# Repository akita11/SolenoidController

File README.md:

# SolenoidController

・ソレノイドやDCモータを4個、制御できるボード。単体でスイッチでON/OFFできる。
・各種マイコン(Arduino, micro:bit, RaspberryPi, IchigoJam, Grove)からも制御できる。
・電源は24Vまで（使用するソレノイドにあわせる）
- オプションで、USB Type-C PDからの給電もできる（検証は不十分）

# Author

Junichi Akita (@akita11, akita@ifdl.jp)

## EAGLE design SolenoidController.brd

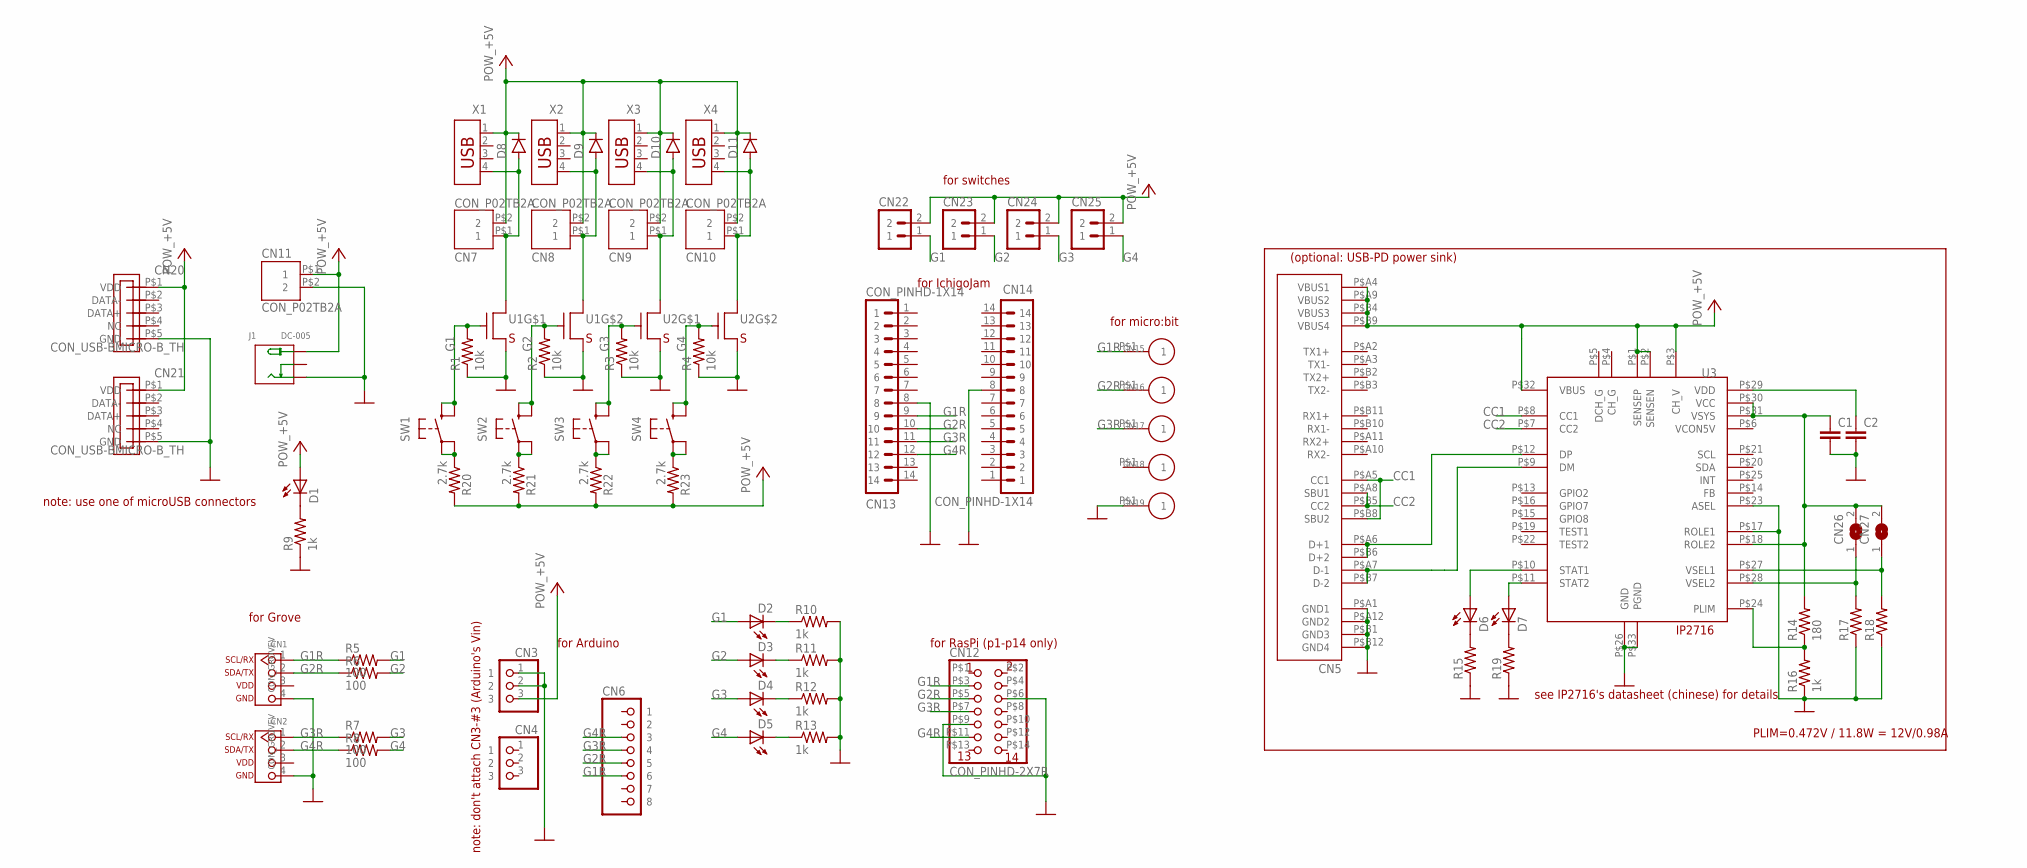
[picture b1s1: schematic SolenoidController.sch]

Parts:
C1, C2: CAP0603; 0603
CN1, CN2: CON_GROVEV; CON_GROVE_V
CN3, CN4: CON_PINHD-1X3R; 1X03R
CN5: CON_USB-C; USB-C_24P
CN6: CON_PINHD-1X8R; 1X08R
CN7, CN8, CN9, CN10, CN11: CON_P02TB2A; TERM_BLOCK_2P
CN12: CON_PINHD-2X7R; 2X7R
CN13, CN14: CON_PINHD-1X14; 1X14
CN15, CN16, CN17, CN18, CN19: CON_P01TH04MM; TH4MM
CN20, CN21: CON_USB-BMICRO-B_TH; USB-MICROB-TH
CN22, CN23, CN24, CN25: CON_PINHD-1X2PTH; SPARKFUN_1X02
CN26, CN27: JUMPER_SJ
D1, D2, D3, D4, D5: LED5MM; SPARKFUN_LED5MM
D6, D7: LED0603; SPARKFUN_LED-0603
D8, D9, D10, D11: DIODESOD123FL; SOD123FL
J1: DC-005; DCJ3P-14.2X11.0X9.0MM
R1, R2, R3, R4: 10k; 0603
R5, R6, R7, R8: 100; 0603
R9, R10, R11, R12, R13, R16: 1k; 0603
R14: 180; 0603
R15, R17, R18, R19: RES0603; 0603
R20, R21, R22, R23: 2.7k; 0603
SW1, SW2, SW3, SW4: SW_TACTSMD_B3FS4; SW_B3FS-4
U1, U2: TR_NMOS_IRF7103; SO08
U3: PMU_IP2716; QFN32E
X1, X2, X3, X4: CON_USB-A; USB-A

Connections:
+5V: CN3.3, CN5.P$A4 (VBUS1), CN5.P$A9 (VBUS2), CN5.P$B4 (VBUS3), CN5.P$B9 (VBUS4), CN7.P$2 (2), CN8.P$2 (2), CN9.P$2 (2), CN10.P$2 (2), CN11.P$1 (1), CN20.P$1 (VDD), CN21.P$1 (VDD), CN22.2, CN23.2, CN24.2, CN25.2, D1.A, D8.P$K, D9.P$K, D10.P$K, D11.P$K, J1.+, R20.2, R21.2, R22.2, R23.2, U3.P$1 (SENSEP), U3.P$2 (SENSEN), U3.P$3 (CH_V), U3.P$32 (VBUS), X1.1, X2.1, X3.1, X4.1
CC1: CN5.P$A5 (CC1), CN5.P$B8 (SBU2), U3.P$8 (CC1)
CC2: CN5.P$A8 (SBU1), CN5.P$B5 (CC2), U3.P$7 (CC2)
G1: CN22.1, D2.A, R1.2, R5.2, SW1.P$3 (S), SW1.P$4 (S1), U1.2 (G)
G1R: CN1.1, CN6.6, CN12.P$3 (3), CN13.9, CN15.P$1, R5.1
G2: CN23.1, D3.A, R2.2, R6.2, SW2.P$3 (S), SW2.P$4 (S1), U1.4 (G)
G2R: CN1.2, CN6.5, CN12.P$5 (5), CN13.10, CN16.P$1, R6.1
G3: CN24.1, D4.A, R3.2, R7.2, SW3.P$3 (S), SW3.P$4 (S1), U2.2 (G)
G3R: CN2.1, CN6.4, CN12.P$7 (7), CN13.11, CN17.P$1, R7.1
G4: CN25.1, D5.A, R4.2, R8.2, SW4.P$3 (S), SW4.P$4 (S1), U2.4 (G)
G4R: CN2.2, CN6.3, CN12.P$11 (11), CN13.12, R8.1
GND: C1.2, C2.2, CN1.4, CN2.4, CN3.1, CN3.2, CN5.P$A1 (GND1), CN5.P$A12 (GND2), CN5.P$B1 (GND3), CN5.P$B12 (GND4), CN11.P$2 (2), CN12.P$6 (6), CN12.P$9 (9), CN13.8, CN14.8, CN19.P$1, CN20.P$5 (GND), CN21.P$5 (GND), J1.-1 (-), R1.1, R2.1, R3.1, R4.1, R9.1, R10.2, R11.2, R12.2, R13.2, R15.1, R16.1, R17.1, R18.1, R19.1, U1.1 (S), U1.3 (S), U2.1 (S), U2.3 (S), U3.P$17 (ROLE1), U3.P$23 (ASEL), U3.P$26 (GND), U3.P$33 (PGND)
unnamed: CN7.P$1 (1), D8.P$A, U1.7 (D), X1.4
unnamed: CN8.P$1 (1), D9.P$A, U1.5 (D), X2.4
unnamed: CN9.P$1 (1), D10.P$A, U2.7 (D), X3.4
unnamed: C2.1, U3.P$29 (VDD)
unnamed: D1.K (C), R9.2
unnamed: D2.K (C), R10.1
unnamed: R14.1, R16.2, U3.P$24 (PLIM)
unnamed: D3.K (C), R11.1
unnamed: CN26.1, R17.2, U3.P$28 (VSEL2)
unnamed: D4.K (C), R12.1
unnamed: R21.1, SW2.P$1, SW2.P$2 (P1)
unnamed: D5.K (C), R13.1
unnamed: CN27.1, R18.2, U3.P$27 (VSEL1)
unnamed: C1.1, CN26.2, CN27.2, R14.2, U3.P$18 (ROLE2), U3.P$30 (VCC), U3.P$31 (VSYS)
unnamed: D6.C, R15.2
unnamed: CN10.P$1 (1), D11.P$A, U2.5 (D), X4.4
unnamed: D7.C, R19.2
unnamed: D7.A, U3.P$11 (STAT2)
unnamed: D6.A, U3.P$10 (STAT1)
unnamed: CN5.P$A6 (D+1), CN5.P$B6 (D+2), U3.P$12 (DP)
unnamed: R23.1, SW4.P$1, SW4.P$2 (P1)
unnamed: CN5.P$A7 (D-1), CN5.P$B7 (D-2), U3.P$9 (DM)
unnamed: R22.1, SW3.P$1, SW3.P$2 (P1)
unnamed: R20.1, SW1.P$1, SW1.P$2 (P1)

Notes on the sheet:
for RasPi (p1-p14 only)
PLIM=0.472V / 11.8W = 12V/0.98A
for switches
note: use one of microUSB connectors
for Grove
note: don't attach CN3-#3 (Arduino's Vin)
for Arduino
for micro:bit
for IchigoJam
IP2716
see IP2716's datasheet (chinese) for details
(optional: USB-PD power sink)

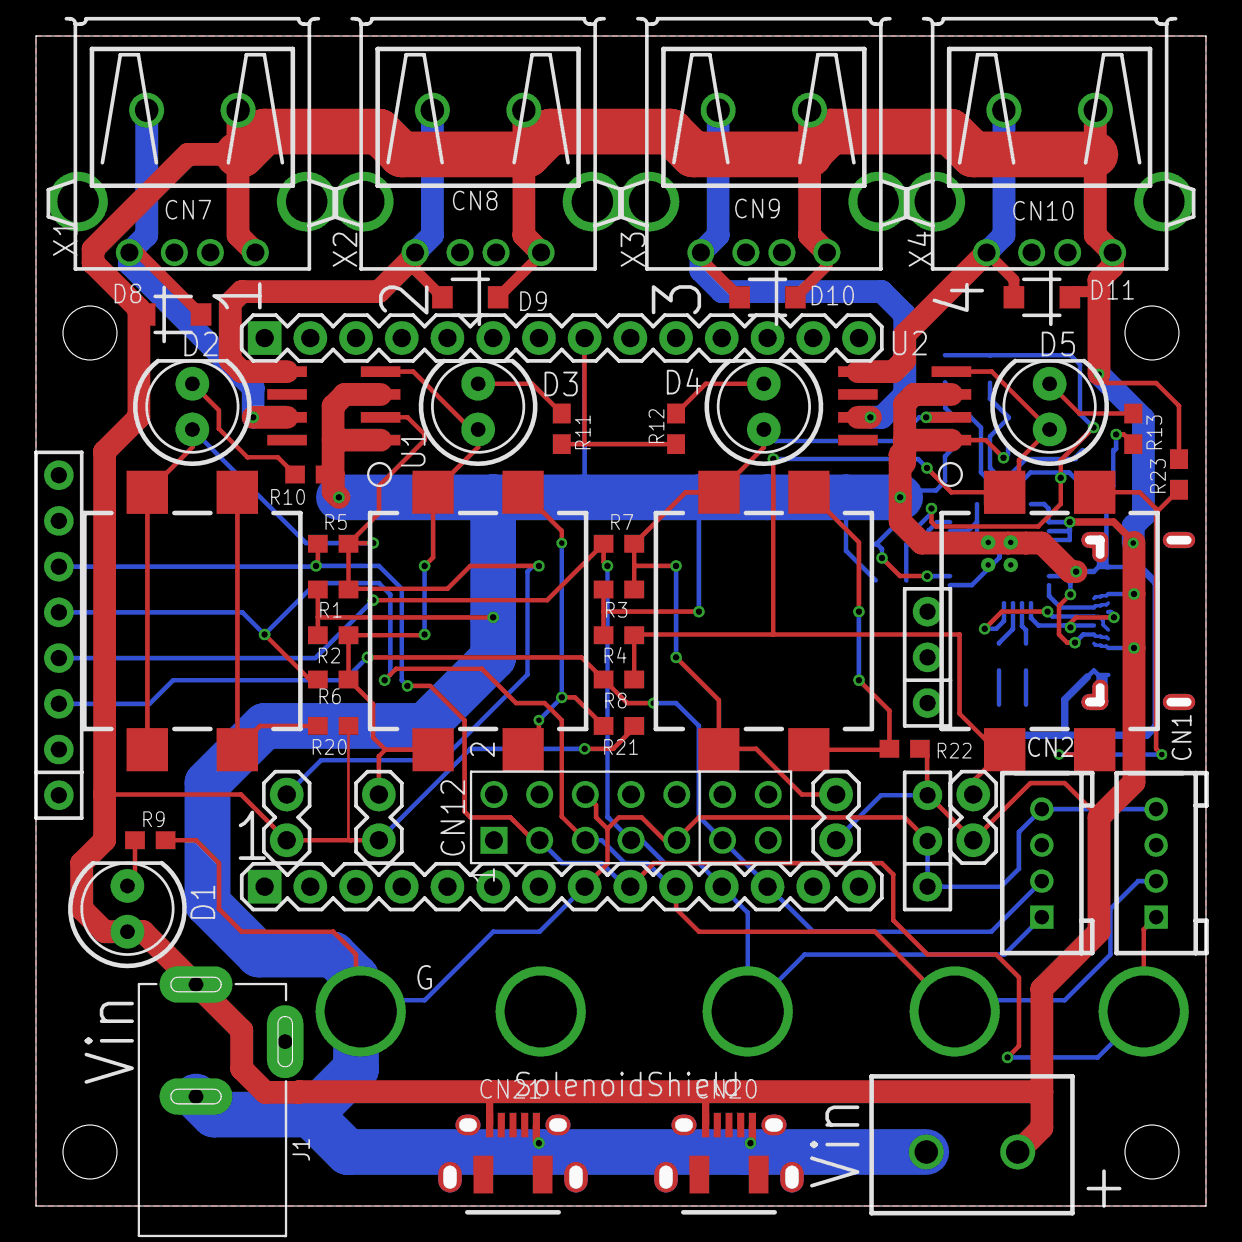
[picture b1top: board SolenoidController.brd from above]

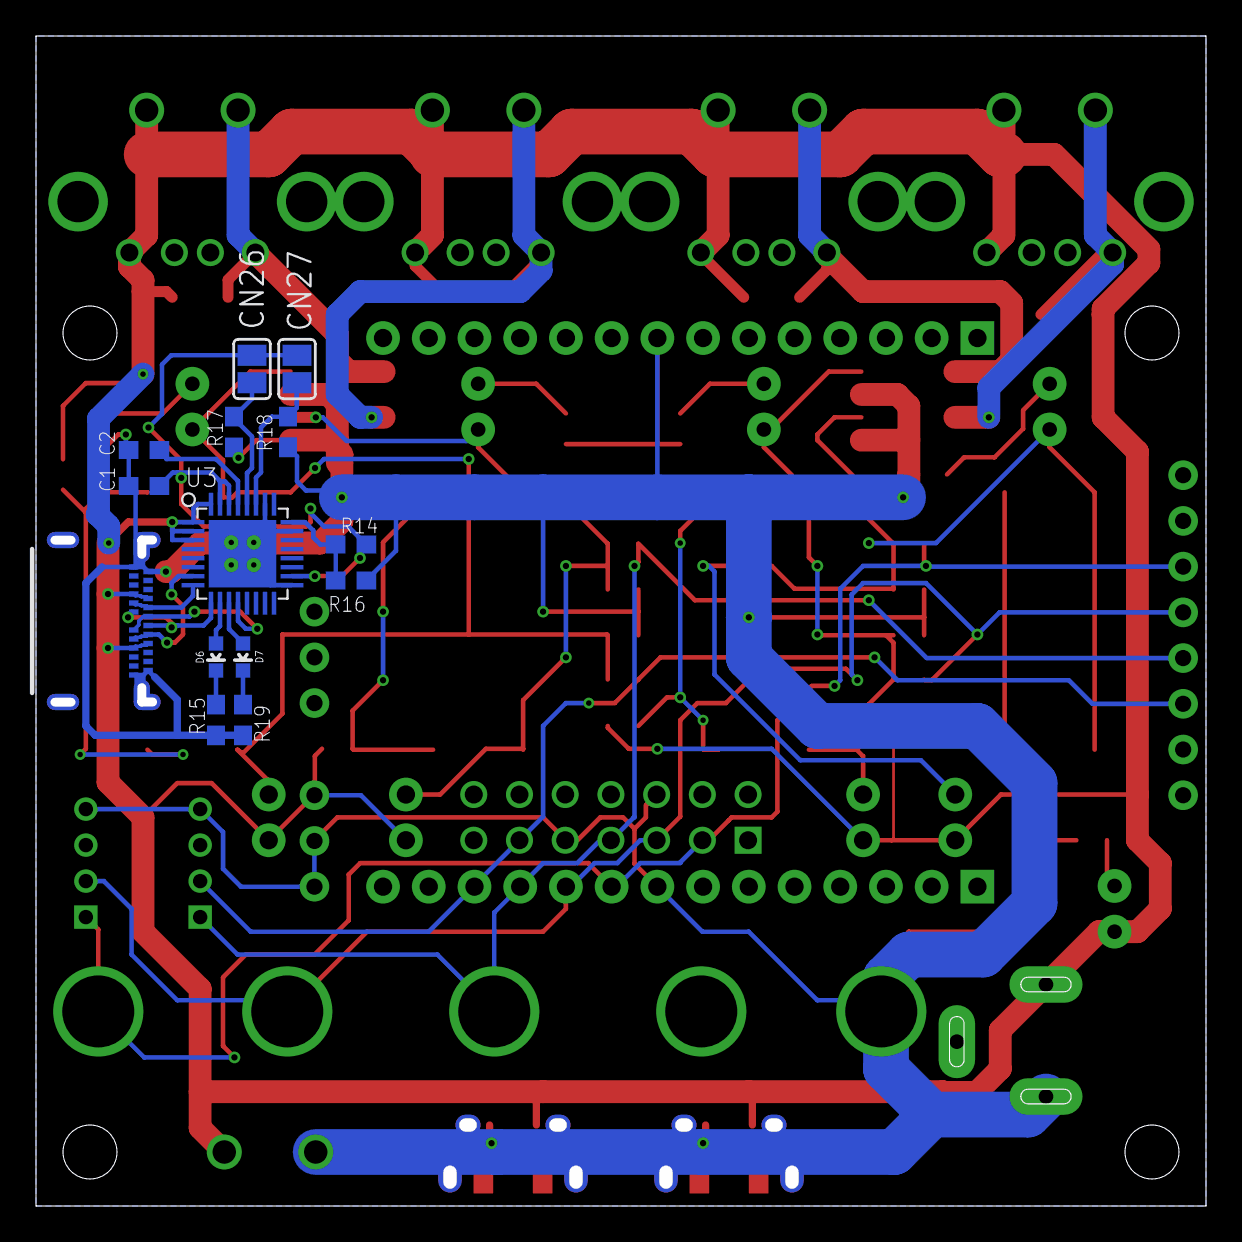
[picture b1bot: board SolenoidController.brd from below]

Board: 2 copper layers, 65.0 x 65.0 mm, 75 parts (14 on the bottom side), 36 nets.

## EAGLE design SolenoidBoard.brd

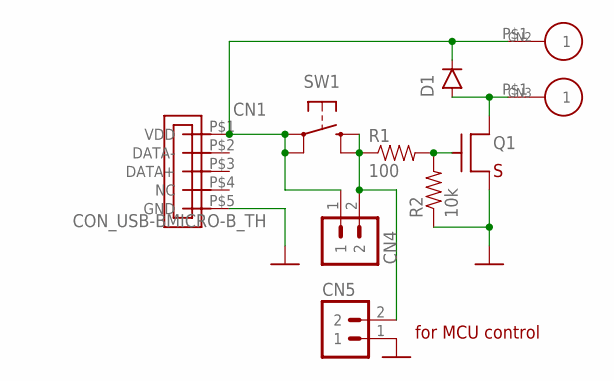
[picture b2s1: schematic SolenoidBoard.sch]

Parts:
CN1: CON_USB-BMICRO-B_TH; USB-MICROB-TH
CN2, CN3: CON_P01TH09MM; PAD_TH09MM
CN4: CON_PINHD-1X290; 1X02/90
CN5: CON_PINHD-1X2PTH; SPARKFUN_1X02
D1: DIODESOD123FL; SOD123FL
Q1: TR_NMOS_IRLML6344; SOT-23-3-2916
R1: 100; 0603
R2: 10k; 0603
SW1: SW_TACTSMD_B3FS; SW_B3FS-1

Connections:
GND: CN1.P$5 (GND), CN5.1, Q1.2 (S), R2.1
unnamed: CN3.P$1, D1.P$A, Q1.3 (D)
unnamed: CN1.P$1 (VDD), CN2.P$1, CN4.1, D1.P$K, SW1.P$1, SW1.P$2 (P1)
unnamed: Q1.1 (G), R1.2, R2.2
unnamed: CN4.2, CN5.2, R1.1, SW1.P$3 (S), SW1.P$4 (S1)

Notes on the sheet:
for MCU control

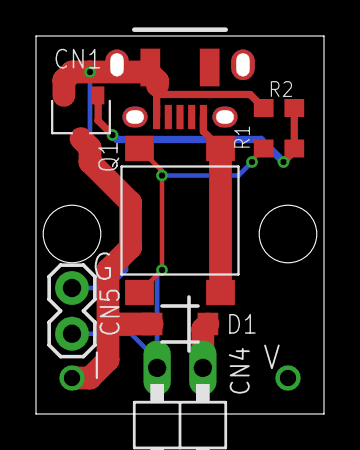
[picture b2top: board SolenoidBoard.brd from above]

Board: 2 copper layers, 16.0 x 21.0 mm, 10 parts (0 on the bottom side), 5 nets.

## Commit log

2019-08-27 各種データのinitial commit
2019-08-27 brdの差し替え
